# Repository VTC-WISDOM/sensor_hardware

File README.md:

# sensor_hardware
Hardware of peripherals to the node

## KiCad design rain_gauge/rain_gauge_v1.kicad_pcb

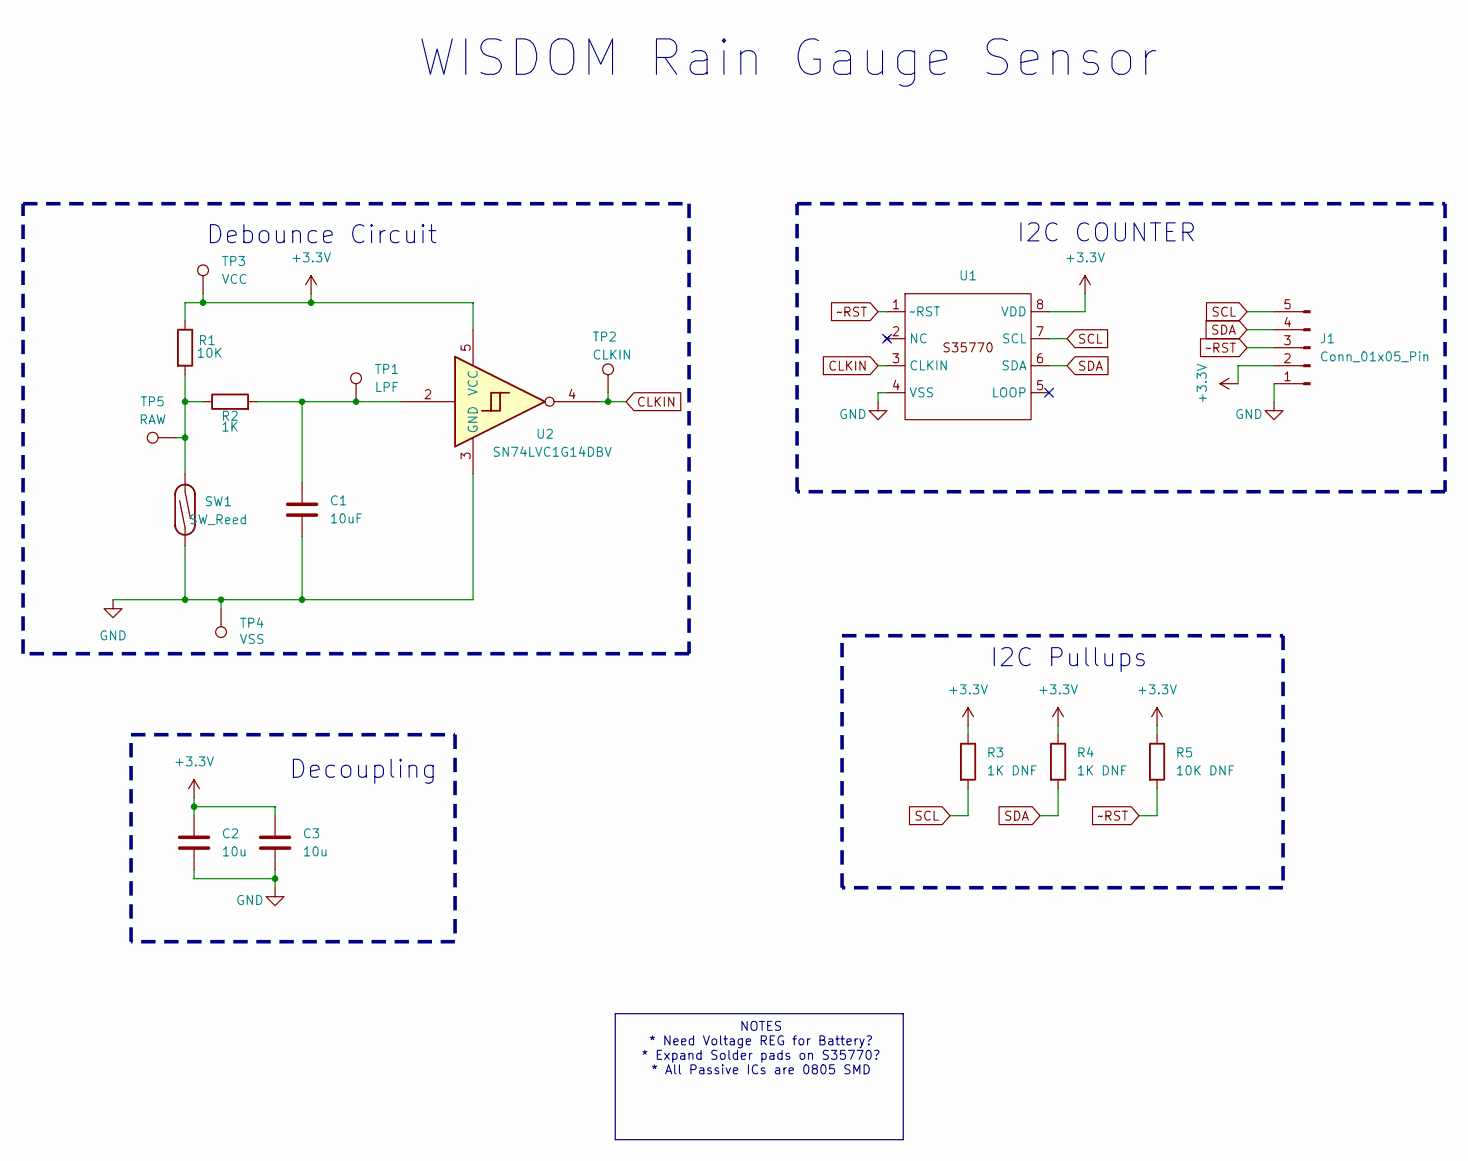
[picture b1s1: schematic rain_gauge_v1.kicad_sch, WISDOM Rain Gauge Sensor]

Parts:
C1: 10uF; C_0805_2012Metric_Pad1.18x1.45mm_HandSolder
C2, C3: 10u; C_0805_2012Metric_Pad1.18x1.45mm_HandSolder
J1: Conn_01x05_Pin; JST_EH_B5B-EH-A_1x05_P2.50mm_Vertical
R1: 10K; R_0805_2012Metric_Pad1.20x1.40mm_HandSolder
R2: 1K; R_0805_2012Metric_Pad1.20x1.40mm_HandSolder
R3, R4: 1K DNF; R_0805_2012Metric_Pad1.20x1.40mm_HandSolder
R5: 10K DNF; R_0805_2012Metric_Pad1.20x1.40mm_HandSolder
SW1: SW_Reed; SW_SPST_REED_CT05-XXXX-J1
TP1: LPF; PinHeader_1x01_P2.54mm_Vertical
TP2: CLKIN; PinHeader_1x01_P2.54mm_Vertical
TP3: VCC; PinHeader_1x01_P2.54mm_Vertical
TP4: VSS; PinHeader_1x01_P2.54mm_Vertical
TP5: RAW; PinHeader_1x01_P2.54mm_Vertical
U1: S35770; TMSOP08_2P9X2P8_ABL
U2: SN74LVC1G14DBV; SOT-23-5

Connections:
+3.3V: C2.1, C3.1, J1.2, R1.1, R3.1, R4.1, R5.1, TP3.1, U1.8 (VDD), U2.5 (VCC)
CLKIN: TP2.1, U1.3 (CLKIN), U2.4
GND: C1.2, C2.2, C3.2, J1.1, SW1.2, TP4.1, U1.4 (VSS), U2.3 (GND)
unnamed: C1.1, R2.2, TP1.1, U2.2
unnamed: R1.2, R2.1, SW1.1, TP5.1
SCL: J1.5, R3.2, U1.7 (SCL)
SDA: J1.4, R4.2, U1.6 (SDA)
~RST: J1.3, R5.2, U1.1 (~RST)

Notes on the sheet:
Debounce Circuit
I2C Pullups
Decoupling
NOTES * Need Voltage REG for Battery? * Expand Solder pads on S35770? * All Passive ICs are 0805 SMD
WISDOM Rain Gauge Sensor
I2C COUNTER

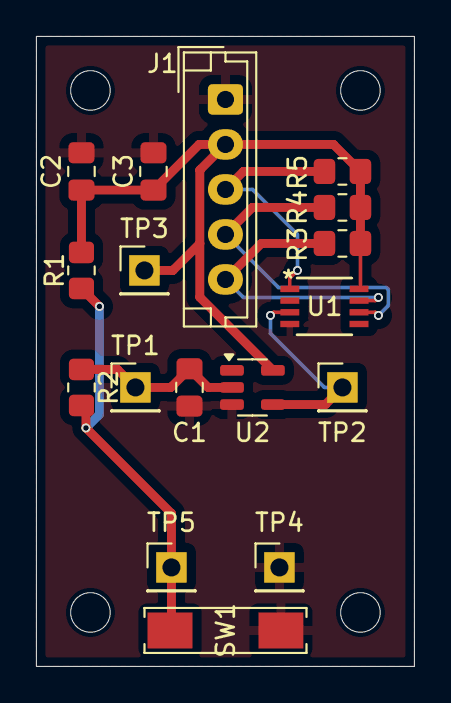
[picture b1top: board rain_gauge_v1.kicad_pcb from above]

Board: 2 copper layers, 21.0 x 35.0 mm, 17 parts (0 on the bottom side), 8 nets.

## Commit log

2024-08-13 initial
2024-08-13 remove regulator, add decoupling, add pullups
2024-08-20 Rain Gauge V2
